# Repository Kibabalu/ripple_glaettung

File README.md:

# ripple_glaettung

suppress voltage ripple of power sources

A KiCAD project.

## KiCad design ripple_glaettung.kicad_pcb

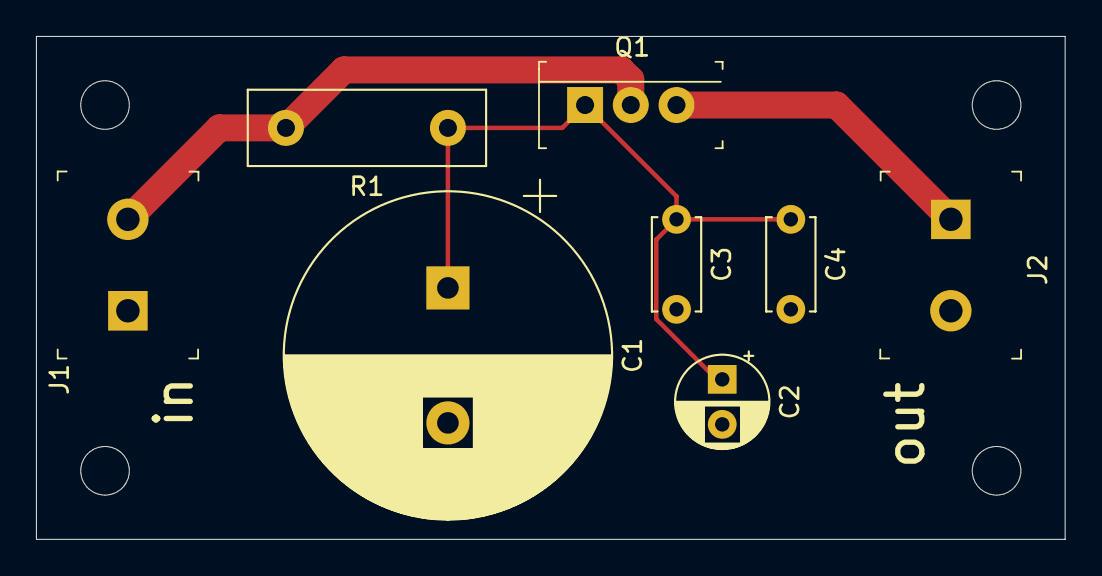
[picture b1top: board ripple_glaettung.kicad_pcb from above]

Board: 2 copper layers, 57.1 x 27.9 mm, 12 parts (0 on the bottom side), 4 nets.

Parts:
 : MountingHole_2.7mm
 #2,  #3,  #4: MountingHole_2.7mm
C1: 4700u; CP_Radial_D18.0mm_P7.50mm
C2: 47u; CP_Radial_D5.0mm_P2.50mm
C3: 100n; C_Disc_D5.0mm_W2.5mm_P5.00mm
C4: 1n; C_Disc_D5.0mm_W2.5mm_P5.00mm
J1, J2: Term_Block_1x2_P5.08MM
Q1: MJE3055T; TO-220-3
R1: 10; R_Box_L13.0mm_W4.0mm_P9.00mm

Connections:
GND: C1.2, C2.2, C3.2, C4.2, J1.1, J2.2
unnamed: C1.1, C2.1, C3.1, C4.1, Q1.1, R1.1
unnamed: J2.1, Q1.3
VCC: J1.2, Q1.2, R1.2

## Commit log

2020-06-05 1st commit
2020-06-06 minor change
2020-06-07 fine tuning pcb picture
2020-06-14 picture added
2020-06-14 added recommendation for TIP142 Darlington
